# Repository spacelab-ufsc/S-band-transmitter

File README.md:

<h1 align="center">
	TRANSMITTER FOR S-BAND
	<br>
</h1>

<h4 align="center">Transmitter module designed to operate on S-band</h4>

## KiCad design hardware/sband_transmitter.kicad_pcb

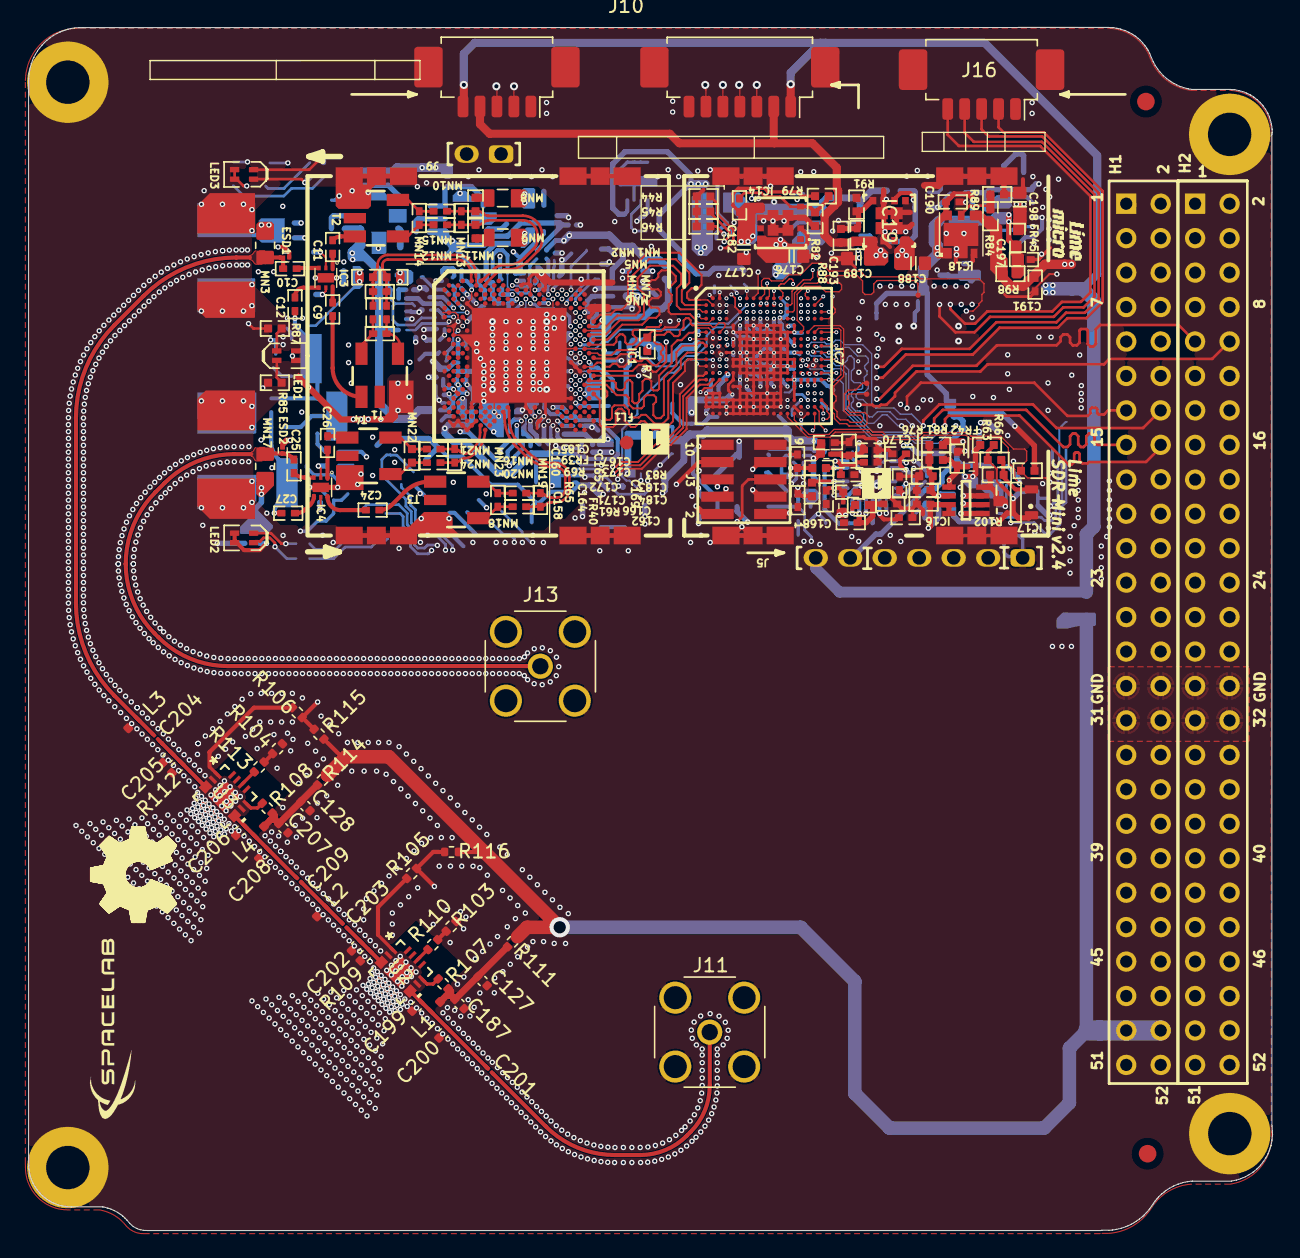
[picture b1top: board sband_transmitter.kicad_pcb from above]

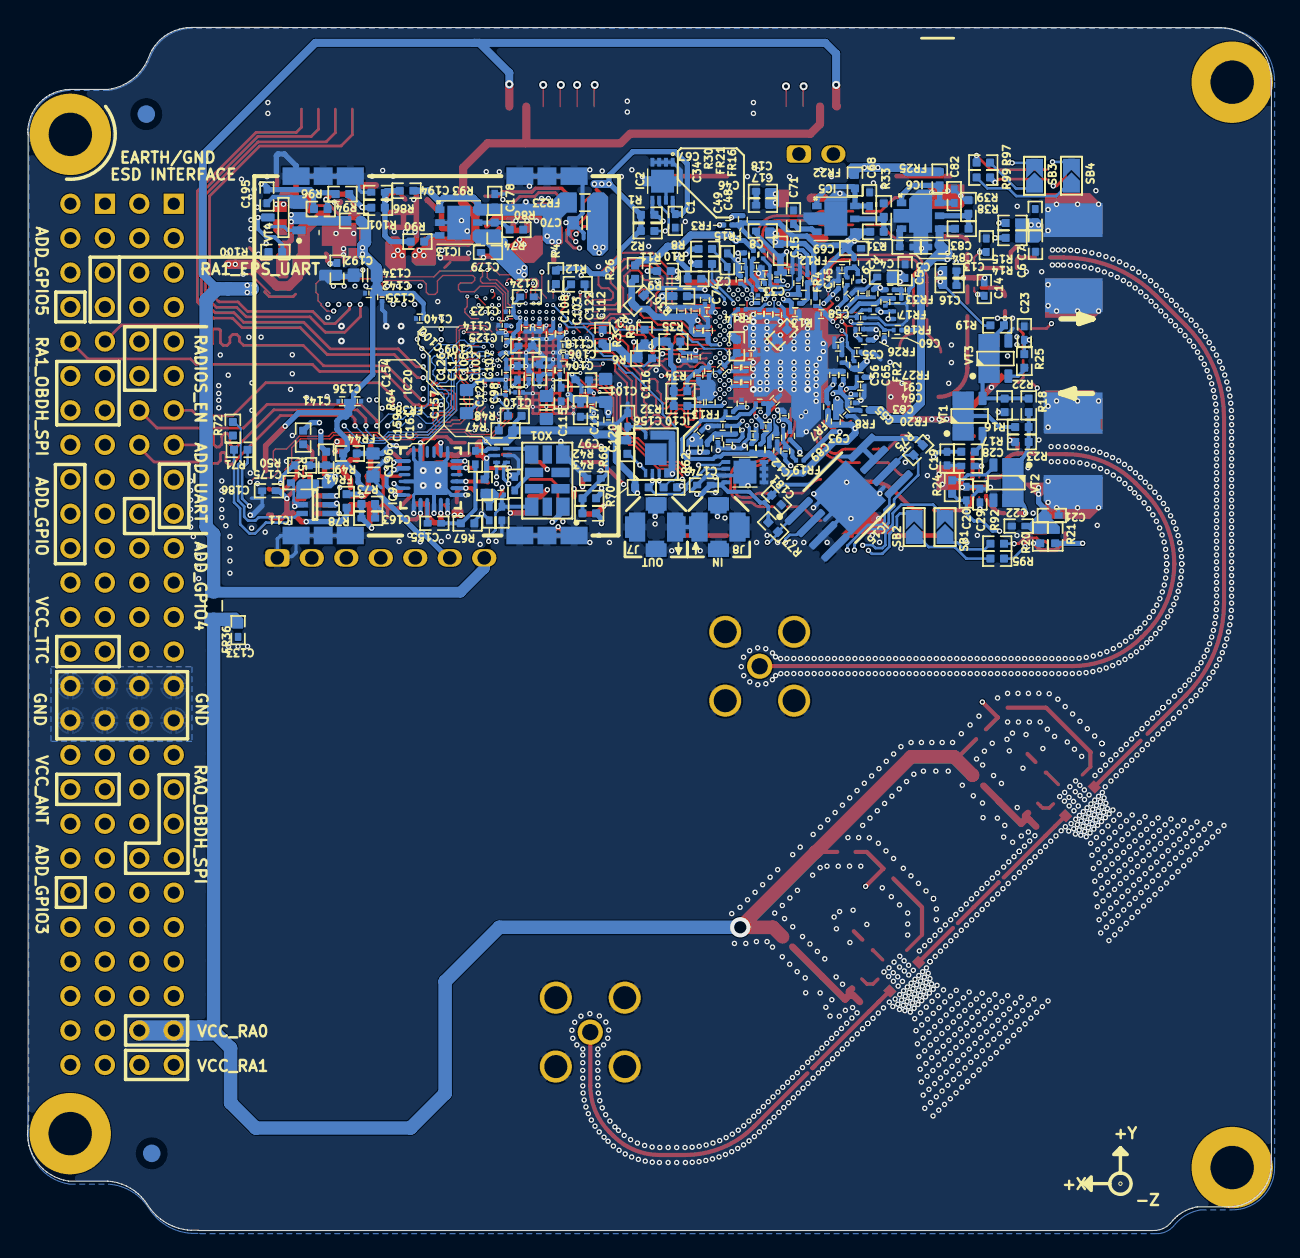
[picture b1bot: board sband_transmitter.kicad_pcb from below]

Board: 8 copper layers, 91.7 x 88.7 mm, 434 parts (278 on the bottom side), 218 nets.

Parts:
C1, C159, C164, C165, C194: 1uF, 25V; CAP0402
C2: 10pF, 25V; CAP0402
C3, C5, C7, C16, C17, C19, C20, C22, C23, C71, C84, C167, C168, C169, C170, C172, C173, C192: 100pF, 50V; CAP0402
C4, C6, C8, C15, C18, C21, C97, C133, C154, C155, C156, C161, C162, C163, C166, C171, C174, C175, C180, C181, C183, C185, C186, C195: 100nF, 16V; CAP0402
C9, C12, C24, C27, C158, C160: 47pF, 50V; CAP0402
C10, C11, C25, C26: 510pF; CAP0402
C13, C14, C28, C29, C102, C104, C109, C113, C115, C119, C124: 10nF, 50V; CAP0402
C30, C32, C33, C34, C35, C36, C37, C39, C41, C43, C44, C45, C46, C48, C49, C50, C51, C52, C53, C54, C55, C56, C57, C58, C59, C60, C62, C63, C64, C65, C66, C67, C73, C75, C77, C79, C81, C85, C86, C87, C88, C89, C90, C91, C92, C93, C94, C95, C96, C100, C111, C117, C122, C135, C141: 1uF, 6.3V; CAP0201
C31, C38, C40, C42, C47, C61, C72, C74, C76, C78, C80: 1nF, 10%; CAP0201
C68, C69, C82, C83, C178, C179, C190, C191, C197: 4.7uF, 6.3V; CAP0402
C70, C99, C116, C121, C134, C196, C198: 10uF, 6.3V; CAP0603
C98, C101, C103, C105, C106, C107, C108, C110, C112, C114, C118, C120, C123, C125, C126, C136, C140, C142: 100nF, 10V; CAP0201
C127, C128: 0.1uF; C_0402_1005Metric
C157: 18nF, 16V; CAP0402
C176, C177, C188, C189: 22uF, 10V; CAP0603
C182: 16pF, 50V; CAP0402
C184: 1nF, 50V; CAP0402
C187, C207: 100pF; C_0402_1005Metric
C193: 82pF, 50V; CAP0402
C199, C200, C206, C208: 1.5pF; C_0402_1005Metric
C201, C209: 27pF; C_01005_0402Metric
C202, C205: 2pF; C_0402_1005Metric
C203, C204: 1pF; C_01005_0402Metric
ESD1, ESD2: ESD8472; ESD8472_X3DFN2
FL1: Fiducial; Fiducial_local
FR1, FR2, FR3, FR4, FR5, FR6, FR7, FR8, FR9, FR10, FR11, FR12, FR13, FR14, FR15, FR16, FR17, FR18, FR19, FR20, FR21, FR24, FR26, FR27, FR28, FR29, FR30, FR31, FR32, FR33, FR34, FR38, FR39, FR40, FR41, FR42: 600R, 0.27A; RES0201
FR22, FR25, FR44, FR45: 220R, 0.9A; RES0402
FR23, FR36: 600R, 2A; RES0805
IC1: LMS7002M; LMS7002M_v5
IC2, IC12: M24128; M24128-DFMC6TG
IC3, IC4: SKY13411-374LF
IC5, IC6, IC13, IC18: LD39100PUR
IC7: LFE5U-45F-MG285; LFE5U-25F-8MG285C_LATTICE_FPGA
IC9: LMK00105; LMK00105SQ
IC10: LM75; HWSON8_LM75
IC11: DAC6311IDCK; AD5601_SOT23-6
IC14: LMZ20501SILR; LMZ20501SILR_DC-DC_8-SMD
IC15: W25Q128JVSIQ; S25FL164K_WSON8_DFN6
IC16: AD5662; AD5662_SOT23-8
IC17: AS431; SOT23-3_V3
IC19: LMZ20501SILR; SIL0008F
IC20: 74LVC1G3157FZ4; 74LVC1G3157FZ4_SPDT_SW_DFN1410-6
J3: FPGA GPIO; SWD_10_pin
J5: FPGA JTAG (board edge); HEADER7X1_TH_V2
J7, J8: U.FL/MMCX; MMCX_UFL_conn_u
J9: FAN; Header2x1_TH_v2
J10: PC104-Mainboard
J11, J13: Conn_Coaxial; CONN MCX JACK RA 50 OHM SMD
J12: FPGA JTAG (board edge); Molex_PicoBlade_53261-0771_1x07-1MP_P1.25mm_Horizontal
J15, J16: FPGA EGPIO (board edge); Molex_PicoBlade_53261-0571_1x05-1MP_P1.25mm_Horizontal
L1, L4: 18nH; L_0402_1005Metric
L2, L3: 6.2nH; L_0402_1005Metric
LED1, LED2, LED3: LED_RG; LED-2x0603
MECH2, MECH3, MECH4, MECH5, MECH6, MECH7, MECH8, MECH9, MECH11, MECH12, MECH13, MECH14: RFI Shield clip; RFI_SHIELD_CLPS_MINI
MECH10: RFI Shield; WurthElectronic_RF_shield
MECH15: RFI Shield; WURTHELECTRONIC_RF_SHIELD
MN1, MN2, MN22: 8.2nH, 5%; RES0402
MN3, MN17: 100uH; RES0805_0603
MN4, MN7: 0.8pF; CAP0402
MN5, MN13, MN19: 1pF; CAP0402
MN6, MN18: 0.5pF; CAP0402
MN8, MN9: 100uH; RES0805
MN10, MN11: 0R; RES0402
MN12, MN15: 100nF, 16V; CAP0402
MN14, MN16, MN20: 2pF; CAP0402
MN21, MN24: 510pF; CAP0402
MN23: 1.2pF; CAP0402
R1, R2: 2k2, 1%; RES0402
R3, R4, R5, R6, R7, R12, R13, R39, R62, R71, R73, R74, R77, R83, R84, R86: 10k, 1%; RES0402
R8, R9, R10, R11, R22, R23, R67: 49.9R, 1%; RES0402
R14, R15, R20, R21, R26, R27, R32, R34, R35, R36, R37, R42, R43, R44, R45, R46, R61, R65, R66, R69, R78, R90, R94, R96, R98, R100, R101, R102: 0R; RES0402
R16: 560R, 1%; RES0402
R17, R24, R25, R85, R87, R92, R95, R97, R99: 100R, 1%; RES0402
R18: 2.49k, 1%; RES0402
R19, R63, R68, R70, R75, R81: 1k, 1%; RES0402
R28, R29, R40, R41: 10R; RES0201
R30: 0R; RES0201
R31: 8.2k, 1%; RES0402
R33: 15k, 1%; RES0402
R38: 7.5k, 1%; RES0402
R47, R48, R49, R50, R51, R52, R89, R93: 4K7, 1%; RES0402
R64: 22R; RES0402
R72, R76: 3k, 1%; RES0402
R79: 80.6k, 1%; RES0402
R80: 27k, 1%; RES0402
R82: 40.2k, 1%; RES0402
R88: 237k, 1%; RES0402
R91: 52.3k, 1%; RES0402
R103, R104: 100k; R_0402_1005Metric
R105, R106: 22k; R_0402_1005Metric
R107, R108: 50R; R_0402_1005Metric
R109, R112: 15K; R_0402_1005Metric
R110, R111, R113, R114, R115, R116: 0R; R_0402_1005Metric
SB1, SB2, SB3, SB4: Solder bridge; SOLDER_BRIDGE_TRIANGULAR_V2
T1, T2, T3, T4: TC1-1-13M-45+; TC1-1-13MA+_JA4220-AL_
U2, U3: GRF5115; QFN-16_GRF
VT1, VT2, VT3: ZVN4525E6TA; ZVN4525E6_NMOS_SOT23-6
VT4: IRLML6244TRPBF; SOT23-3
XO1: E7355LF, 40MHz, w VC; RAKON_RTX5032A

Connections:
+1.8V_DIG_LMK: C164.2, C171.2, C172.2, C173.2, FR40.2, IC9.2 (Vddo), IC9.6 (Vddo)
+3.3V_DIG_LMK: C165.2, C166.2, C167.2, C168.2, C169.2, C170.2, FR39.2, IC9.8 (Vdd), IC9.14 (Vddo), IC9.18 (Vddo), IC9.23 (Vdd), R61.2
/05_LMS7002M_Misc/LMS_CORE_LDO_EN: IC1.U33 (CORE_LDO_EN), R7.1
/05_LMS7002M_Misc/LMS_I2C_SCL: IC1.C27 (SCL), IC2.6 (SCL), R2.2
/05_LMS7002M_Misc/LMS_I2C_SDA: IC1.D26 (SDA), IC2.5 (SDA), R1.2
/05_LMS7002M_Misc/LMS_RESET: IC1.E27 (RESET), R4.1
/05_LMS7002M_Misc/LMS_RXEN: IC1.V34 (RXEN), R6.2
/05_LMS7002M_Misc/LMS_TXEN: IC1.U29 (TXEN), R5.2
/05_LMS7002M_Misc/LMS_TXNRX1: IC1.V32 (TXNRX1), R3.1
/05_LMS7002M_Misc/LMS_TXNRX2: IC1.U31 (TXNRX2), R12.1
/06_LMS7002M_RF/RFSW_RX_V1: C29.2, IC4.5 (V1)
/06_LMS7002M_RF/RFSW_RX_V2: C28.2, IC4.2 (V2)
/06_LMS7002M_RF/RFSW_TX_V1: C14.2, IC3.5 (V1)
/06_LMS7002M_RF/RFSW_TX_V2: C13.2, IC3.2 (V2)
/06_LMS7002M_RF/RX: C25.2, ESD2.1, J13.1 (In), MN17.1
/06_LMS7002M_RF/RX1_H: C24.2, T3.3
/06_LMS7002M_RF/RX1_H_A_N: IC1.AJ15 (rfgn_h_RFE_1), MN19.1, MN20.2
/06_LMS7002M_RF/RX1_H_A_P: IC1.AK14 (rfgp_h_RFE_1), MN16.2, MN19.2
/06_LMS7002M_RF/RX1_H_B_N: MN18.1, MN20.1, T3.6
/06_LMS7002M_RF/RX1_H_B_P: MN16.1, MN18.2, T3.4
/06_LMS7002M_RF/RX1_W: C26.2, T4.3
/06_LMS7002M_RF/RX1_W_A_N: IC1.AP10 (rfgn_w_RFE_1), MN23.1, MN24.2
/06_LMS7002M_RF/RX1_W_A_P: IC1.AN9 (rfgp_w_RFE_1), MN21.2, MN23.2
/06_LMS7002M_RF/RX2_W_B_N: MN22.1, MN24.1, T4.6
/06_LMS7002M_RF/RX2_W_B_P: MN21.1, MN22.2, T4.4
/06_LMS7002M_RF/TX1_1: C9.2, T1.3
/06_LMS7002M_RF/TX1_1_A_N: IC1.A7 (pa1on_1), MN1.1, MN5.1, MN7.2
/06_LMS7002M_RF/TX1_1_A_P: IC1.B8 (pa1op_1), MN2.1, MN4.1, MN5.2
/06_LMS7002M_RF/TX1_1_B_N: MN6.2 (2_2), MN7.1, T1.6
/06_LMS7002M_RF/TX1_2: C11.2, T2.1
/06_LMS7002M_RF/TX2_1_A_N: IC1.B10 (pa2on_1), MN10.1, MN13.2, MN15.1
/06_LMS7002M_RF/TX2_1_A_P: IC1.A9 (pa2op_1), MN11.1, MN12.2, MN13.1
/06_LMS7002M_RF/TX2_1_B_N: MN14.1, MN15.2, T2.4
/06_LMS7002M_RF/TX2_1_B_P: MN12.1, MN14.2, T2.6
/06_LMS7002M_RF/TX_LB_AT: C19.1, R17.2
/06_LMS7002M_RF/TX_LB_SH: C20.1, C23.1, R24.1, R25.2
/08_FPGA/BOM_VER0: IC7.N1 (PR47D/LRC_GPLL0C_IN), R44.2
/08_FPGA/BOM_VER1: IC7.M1 (PR47C/LRC_GPLL0T_IN), R45.2
/08_FPGA/BOM_VER2: IC7.N2 (PR44D), R46.2
/08_FPGA/FPGA_EGPIO1: IC7.A8 (PT35B/PCLKC1_0), J15.3
/08_FPGA/FPGA_GPIO2: IC7.N16 (PB4B/D6/IO6), J3.3
/08_FPGA/FPGA_GPIO3: IC7.N17 (PB6A/D5/IO5), J3.4
/08_FPGA/FPGA_GPIO4: IC7.M18 (PB6B/D4/IO4), J3.5
/08_FPGA/FPGA_GPIO5: IC7.R18 (PB9B/D2/IO2), J3.6
/08_FPGA/FPGA_GPIO6: IC7.T17 (PB13B/CS1N), J3.7
/08_FPGA/FPGA_GPIO7: IC7.R17 (PB13A/SN/CSN), J3.8
/08_FPGA/FPGA_JTAG_TCK: IC7.U13 (TCK), J5.2, J12.6, R52.1 (1_1)
/08_FPGA/FPGA_JTAG_TDI: IC7.T13 (TDI), J5.5, J12.5, R49.2
/08_FPGA/FPGA_JTAG_TDO: IC7.V14 (TDO), J5.3, J12.3, R51.2
/08_FPGA/FPGA_JTAG_TMS: IC7.V13 (TMS), J5.4, J12.4, R50.2
/10_Misc/EN_VCC3P3: C194.2, IC19.2 (EN), R86.1, R90.2, R93.1
/10_Misc/FPGA_CFG_SPI_SCLK: IC15.6 (C), R75.1
/10_Misc/FPGA_CFG_SPI_SS: IC15.1 (S), R77.1
/10_Misc/FPGA_I2C_SCL: IC10.2 (SCL), IC12.6 (SCL), R70.2
/10_Misc/FPGA_I2C_SDA: IC10.1 (SDA), IC12.5 (SDA), R68.2
/10_Misc/FPGA_LED2_G: R92.2, SB1.1
/10_Misc/FPGA_LED2_R: R95.2, SB2.1
/10_Misc/FPGA_LED3_G: R97.2, SB3.1
/10_Misc/FPGA_LED3_R: R99.2, SB4.1
/10_Misc/FPGA_SPI_DAC_SS: IC11.1 (~SYNC), IC16.5 (~SYNC)
/10_Misc/FPGA_SPI_MOSI: IC11.3 (SDIN), IC16.7 (DIN)
/10_Misc/FPGA_SPI_SCLK: IC11.2 (SCLK), IC16.6 (SCLK)
/10_Misc/LM75_OS: IC10.3 (OS), R62.1
/10_Misc/PG_VCC1P1: IC13.3 (PG), R90.1
/10_Misc/REF_CLK_IN: IC20.1 (B1), J8.1 (X)
/10_Misc/REF_CLK_OUT: IC9.17 (CLKout4), J7.1 (X)
/10_Misc/RxPLL_CLK: C160.2, R69.1
/10_Misc/TCXO_DAC_VREF: C183.1, IC16.2 (Vref), R76.1, R78.2, R81.1, R83.1
/10_Misc/TxPLL_CLK: C158.2, R65.1
/10_Misc/XO_VC: C163.2, C184.1, IC16.3 (Vfb), IC16.4 (Vout), R71.1, R72.1, R73.1, XO1.1 (VCO)
/12_RF_Driver_PA/Driver-TX-Out: C203.1, C209.2, L2.1
Driver-Enable: IC7.N18 (PB9A/D3/IO3), J3.2, R106.1, R115.2
GND: C1.2, C2.2, C3.2, C4.1, C5.2, C6.1, C8.1, C13.1, C14.1, C15.1, C16.2, C17.2, C18.1, C19.2, C20.2, C21.1, C22.2, C23.2, C28.1, C29.1, C30.2, C31.2, C32.2, C33.2, C34.2, C35.1, C36.2, C37.2, C38.2, C39.2, C40.2, C41.2, C42.2, C43.2, C44.2, C45.2, C46.2, C47.2, C48.2, C49.1, C50.2, C51.2, C52.2, C53.2, C54.2, C55.2, C56.1, C57.2, C58.1, C59.1, C60.2, C61.2, C62.2, C63.2, C64.2, C65.2, C66.2, C67.2, C68.1, C69.1, C70.1, C71.1, C72.2, C73.2, C74.2, C75.2, C76.2, C77.2, C78.2, C79.2, C80.2, C81.2, C82.1, C83.1, C84.1, C85.2, C86.2, C87.2, C88.2, C89.2, C90.2, C91.2, C92.2, C93.2, C94.2, C95.2, C96.2, C97.1, C98.2, C99.1, C100.1, C101.2, C102.1, C103.2, C104.1, C105.2, C106.2, C107.2, C108.2, C109.1, C110.2, C111.1, C112.2, C113.1, C114.2, C115.1, C116.1, C117.1, C118.2, C119.1, C120.2, C121.1, C122.2, C123.2, C124.1, C125.2, C126.2, C127.2, C128.2, C134.1, C135.1, C136.2, C140.2, C141.1, C142.2, C156.2, C157.1, C158.1, C159.1, C160.1, C161.1, C162.1, C163.1, C164.1, C165.1, C166.1, C167.1, C168.1, C169.1, C170.1, C171.1, C172.1, C173.1, C174.2, C175.2, C176.1, C177.1, C178.1, C179.1, C180.2, C181.2, C183.2, C184.2, C185.1, C186.1, C187.2, C188.1, C189.1, C190.1, C191.1, C192.1, C194.1, C195.2, C196.1, C197.1, C198.1, C199.2, C200.2, C202.2, C205.2, C206.2, C207.2, C208.2, ESD1.2, ESD2.2, IC1.AA31 (DIGPRGND1), IC1.AF32 (DIGPRGND2), IC1.AG29 (DIGPRGND1), IC1.AJ7 (rfsn_l_RFE_2), IC1.AJ9 (rfsp_l_RFE_2), IC1.AJ19 (GND_CP_SXR), IC1.AK12 (rfsn_l_RFE_1), IC1.AK20 (GND_DIV_SXR), IC1.AL13 (rfsp_l_RFE_1), IC1.AL23 (GND_VCO_SXR), IC1.AM4 (rfgn_w_RFE_2), IC1.AM8 (rfgn_h_RFE_2), IC1.AM22 (DGND_SXR), IC1.AN3 (rfgp_w_RFE_2), IC1.AN5 (rfgp_l_RFE_2), IC1.AN7 (rfgp_h_RFE_2), IC1.AN25 (GND_RXBUF), IC1.AP6 (rfgn_l_RFE_2), IC1.B18 (DGND_CGEN), IC1.B20 (GND_CP_CGEN), IC1.C7 (GND_TLOBUF_TRF), IC1.C23 (GND_DIG), IC1.D20 (GND_DIV_CGEN), IC1.E25 (GND_SPI_BUF), IC1.F6 (GND_TXBUF), IC1.G31 (DIGPRGND2), IC1.GND (EP), IC1.H2 (GND_VCO_SXT), IC1.J33 (DIGPRGND1), IC1.K4 (GND_CP_SXT), IC1.L3 (GND_DIV_SXT), IC1.N3 (DGND_SXT), IC1.T30 (DIGPRGND1,2), IC1.V30 (LOGIC_RESET), IC1.W29 (DIGPRGND1), IC1.Y30 (DIGPRGND2), IC2.1 (E0), IC2.2 (E1), IC2.3 (E2), IC2.4 (VSS), IC2.7 (~WC), IC2.PAD, IC3.PAD, IC4.PAD, IC5.2 (GND), IC5.PAD, IC6.2 (GND), IC6.PAD, IC7.B3 (GND), IC7.E5 (GND), IC7.E7 (GND), IC7.E8 (GND), IC7.E9 (GND), IC7.E10 (GND), IC7.E11 (GND), IC7.E12 (GND), IC7.F5 (GND), IC7.F6 (GND), IC7.F7 (GND), IC7.F8 (GND), IC7.F9 (GND), IC7.F10 (GND), IC7.F11 (GND), IC7.F12 (GND), IC7.G2 (GND), IC7.G6 (GND), IC7.G7 (GND), IC7.G8 (GND), IC7.G9 (GND), IC7.G10 (GND), IC7.G11 (GND), IC7.G12 (GND), IC7.H6 (GND), IC7.H7 (GND), IC7.H8 (GND), IC7.H9 (GND), IC7.H10 (GND), IC7.H11 (GND), IC7.H12 (GND), IC7.J3 (PR29C/GR_PCLK3_1), IC7.J6 (GND), IC7.J7 (GND), IC7.J8 (GND), IC7.J9 (GND), IC7.J10 (GND), IC7.J11 (GND), IC7.J12 (GND), IC7.K5 (GND), IC7.K6 (GND), IC7.K7 (GND), IC7.K8 (GND), IC7.K9 (GND), IC7.K10 (GND), IC7.K11 (GND), IC7.L2 (GND), IC7.L5 (GND), IC7.L6 (GND), IC7.L7 (GND), IC7.L8 (GND), IC7.L9 (GND), IC7.L10 (GND), IC7.L11 (GND), IC7.L17 (GND), IC7.M6 (GND), IC7.M7 (GND), IC7.M8 (GND), IC7.M9 (GND), IC7.M10 (GND), IC7.M11 (GND), IC7.N7 (GND), IC7.N8 (GND), IC7.N9 (GND), IC7.N10 (GND), IC7.N11 (GND), IC7.P5 (GND), IC7.P6 (GND), IC7.P8 (GND), IC7.P10 (GND), IC7.P12 (GND), IC7.R1 (GND), IC7.R2 (GND), IC7.R3 (GND), IC7.R10 (GND), IC7.T1 (GND), IC7.T2 (GND), IC7.T3 (GND), IC7.T4 (GND), IC7.T5 (GND), IC7.T6 (GND), IC7.T7 (GND), IC7.T8 (GND), IC7.T9 (GND), IC7.T10 (GND), IC7.T11 (GND), IC7.T12 (GND), IC7.U1 (GND), IC7.U2 (GND), IC7.U3 (GND), IC7.U4 (GND), IC7.U5 (GND), IC7.U6 (GND), IC7.U7 (GND), IC7.U8 (GND), IC7.U9 (GND), IC7.U10 (GND), IC7.U11 (GND), IC7.U12 (GND), IC7.U14 (CFG_0), IC7.V4 (GND), IC7.V5 (GND), IC7.V6 (GND), IC7.V7 (GND), IC7.V8 (GND), IC7.V9 (GND), IC7.V10 (GND), IC7.V15 (CFG_2), IC9.1 (GND), IC9.7 (GND), IC9.11 (GND), IC9.12 (GND), IC9.16 (GND), IC9.19 (GND), IC9.22 (SEL), IC9.25 (GND), IC10.4 (GND), IC10.5 (A2), IC10.6 (A1), IC10.7 (A0), IC11.5 (GND), IC12.1 (E0), IC12.2 (E1), IC12.3 (E2), IC12.4 (VSS), IC12.7 (~WC), IC12.PAD, IC13.2 (GND), IC13.PAD, IC14.3 (MODE), IC14.6 (GND), IC14.PAD (EP_(GND)), IC15.3 (W), IC15.4 (GND), IC15.PAD (GND), IC16.8 (GND), IC17.3 (NC/A), IC18.2 (GND), IC18.PAD, IC19.3 (MODE), IC19.6 (GND), IC20.2 (GND), J3.9, J5.1, J7.2 (Y), J8.2 (Y), J10.H1-29 (Pin_29), J10.H1-30 (Pin_30), J10.H1-31 (Pin_31), J10.H1-32 (Pin_32), J10.H2-29 (Pin_29), J10.H2-30 (Pin_30), J10.H2-31 (Pin_31), J10.H2-32 (Pin_32), J11.2 (Ext), J12.7, J13.2 (Ext), J15.1, J16.1, L2.2, L3.2, MECH2.1 (GND_1), MECH3.1 (GND_1), MECH4.1 (GND_1), MECH5.1 (GND_1), MECH6.1 (GND_1), MECH7.1 (GND_1), MECH8.1 (GND_1), MECH9.1 (GND_1), MECH11.1 (GND_1), MECH12.1 (GND_1), MECH13.1 (GND_1), MECH14.1 (GND_1), R12.2, R13.2, R22.1, R23.1, R33.1, R39.1, R44.1, R45.1, R46.1, R67.1, R73.2, R80.2, R82.1, R83.2, R89.2, R91.1, R100.1, R102.2, R103.1, R104.1, R109.2, R112.2, T1.1, T2.3, T3.1, T4.1, U2.2 (GND/NC), U2.5 (GND/NC), U2.6 (GND/NC), U2.7 (GND/NC), U2.8 (GND/NC), U2.11 (GND/NC), U2.17 (GND), U3.2 (GND/NC), U3.5 (GND/NC), U3.6 (GND/NC), U3.7 (GND/NC), U3.8 (GND/NC), U3.11 (GND/NC), U3.17 (GND), VT2.4 (S), VT3.4 (S), VT4.S, XO1.4 (GND)
GPIO-1: IC7.A16 (PL20B), J16.5
GPIO-2: IC7.D18 (PL26C/PCLKT6_0), J16.4
GPIO-3: IC7.G16 (PL29D), J16.3
GPIO-4: IC7.G18 (PL32A), J16.2
I2C_SCL_DATA: IC7.K15 (PL41D), J10.H2-9 (Pin_9)
I2C_SDA_DATA: IC7.K17 (PL44A), J10.H2-10 (Pin_10)
unnamed: C6.2, C7.1 (1_1), MN3.2, R14.2, R15.2
unnamed: C21.2, C22.1, MN17.2, R20.2, R21.2
unnamed: C27.2, R16.1, R18.2, R23.2, VT2.1 (D), VT2.2 (D), VT2.5 (D), VT2.6 (D)
unnamed: C30.1, C31.1, C37.1, C38.1, C39.1, C40.1, C41.1, C42.1, IC1.AA29 (DIGPRVDD1), IC1.AE29 (DIGPRVDD1), IC1.L33 (DIGPRVDD1), IC1.R31 (DIGPRVDD1), R26.2, R27.2
unnamed: C59.2, FR12.1, R28.2, R29.2
unnamed: C74.1, C75.1, IC1.H32 (DIGPRVDD2), R36.2
unnamed: C76.1, C77.1, IC1.T32 (DIGPRVDD2), R35.2
unnamed: C78.1, C79.1, IC1.W33 (DIGPRVDD2), R34.2
unnamed: C80.1, C81.1, IC1.AH30 (DIGPRVDD2), R32.2
unnamed: C95.1, FR34.2, R41.2
unnamed: C96.1, FR33.1, R40.1
unnamed: C97.2, J3.10, R42.2, R43.2
unnamed: C127.1, C187.1, L1.1, R107.2, R111.2
unnamed: C128.1, C207.1, L4.1, R108.2, R114.2
unnamed: C154.1, C155.2, R67.2
unnamed: C159.2, FR38.1, R64.1
unnamed: C195.1, J9.2, R94.2, R96.2
unnamed: C199.1, C200.1, C201.1, L1.2, U2.9 (RF_OUT/VDD), U2.10 (RF_OUT/VDD)
unnamed: C202.1, C203.2, R109.1, U2.3 (RF_IN), U2.4 (RF_IN)
unnamed: C204.2, C205.1, R112.1, U3.3 (RF_IN), U3.4 (RF_IN)
unnamed: C206.1, C208.1, C209.1, L4.2, U3.9 (RF_OUT/VDD), U3.10 (RF_OUT/VDD)
unnamed: C2.1, IC1.C29 (SCLK), R8.1
unnamed: IC1.F30 (SDIO), R9.1
unnamed: IC1.F28 (SDO), R10.1
unnamed: IC1.D28 (SEN), R11.1
unnamed: IC1.F18 (vr_rext), R13.1
unnamed: C72.1, C73.1, IC1.W31 (DIGPRPOC), R37.2
unnamed: C88.1, FR30.1, IC1.E17 (VDD18_BIAS)
unnamed: C67.1, IC1.D24 (VDD18_DIG), R30.1
unnamed: C91.1, FR27.2, IC1.AE3 (VDD18_TIA_RFE), IC1.AF4 (VDD18_LDO_RX)
unnamed: C92.1, FR26.2, IC1.N1 (VDD18_LDO_TX)
unnamed: C93.1, FR34.1, IC1.AM26 (VDD18_RXBUF)
unnamed: C90.1, FR28.1, IC1.AM18 (VDD18_SXR)
unnamed: C87.1, FR31.1, IC1.D16 (VDD18_TRF)
unnamed: C94.1, FR33.2, IC1.H6 (VDD18_TXBUF)
unnamed: C86.1, FR32.1, IC1.E21 (VDD18_VCO_CGEN)
unnamed: C89.1, FR29.1, IC1.AK22 (VDD18_VCO_SXR)
unnamed: C85.1, FR24.1, IC1.G3 (VDD18_VCO_SXT)
unnamed: C32.1, C33.1, C34.1, FR3.1, IC1.A17 (DVDD_CGEN), IC1.C25 (VDD12_DIG), IC1.F24 (VDD_SPI_BUF)
unnamed: C36.1, FR1.1, IC1.AL21 (DVDD_SXR)
unnamed: C35.2, FR2.1, IC1.M4 (DVDD_SXT)
unnamed: C58.2, FR4.1, IC1.J5 (VDD12O_VCO_SXT), IC1.K6 (VDD12_VCO_SXT)
unnamed: C55.1, FR8.1, IC1.AG5 (VDD12_LNA_RFE)
unnamed: C51.1, IC1.AP26 (VDD12_RXBUF), R29.1
unnamed: C56.2, FR7.1, IC1.AD6 (VDD12_TIA_RFE)
unnamed: C43.1, IC1.G5 (VDD12_TXBUF), R28.1
unnamed: C52.1, FR11.1, IC1.AN23 (VDD12_VCO_SXR)
unnamed: C63.1, C64.1, C65.1, FR20.1, IC1.AD4 (VDD14_RBB), IC1.AF2 (VDD14_TIA_RFE), IC1.AF6 (VDD14_LNA_RFE)
unnamed: C61.1, C62.1, FR21.1, IC1.C21 (VDD14_VCO_CGEN)
unnamed: C60.1, FR18.1, IC1.K2 (VDDO_DIV_SXT), IC1.L5 (VDD_DIV_SXT)
unnamed: C45.1, FR17.1, IC1.D6 (VDDO_TLOBUF_TRF), IC1.F8 (VDD_TLOBUF_TRF)
unnamed: C50.1, FR13.1, IC1.AJ25 (VDD_AFE)
unnamed: C49.2, FR14.1, IC1.F20 (VDD_CP_CGEN)
unnamed: C54.1, FR9.1, IC1.AL19 (VDD_CP_SXR)
unnamed: C57.1, FR5.1, IC1.J3 (VDD_CP_SXT)
unnamed: C47.1, C48.1, FR15.1, IC1.E19 (VDD_DIV_CGEN)
unnamed: C53.1, FR10.1, IC1.AM20 (VDD_DIV_SXR)
unnamed: C66.1, FR19.1, IC1.AN17 (VDD_MXLOBUF_RFE)
unnamed: C44.1, FR6.1, IC1.P4 (VDD_TBB)
unnamed: C46.1, FR16.1, IC1.B16 (VDD_TPAD_TRF)
unnamed: C9.1, IC3.6 (ANT1)
unnamed: C11.1, IC3.1 (ANT2)
unnamed: C10.1, IC3.3 (RX)
unnamed: C12.1, IC3.4 (TX)
unnamed: C24.1, IC4.6 (ANT1)
unnamed: C26.1, IC4.1 (ANT2)
unnamed: C25.1, IC4.3 (RX)
unnamed: C27.1, IC4.4 (TX)
unnamed: IC5.5 (ADJ), R31.1, R33.2
unnamed: C68.2, FR22.2, IC5.1 (EN), IC5.6 (Vin)
unnamed: C71.2, IC5.3 (PG)
unnamed: IC6.5 (ADJ), R38.1, R39.2
unnamed: C82.2, FR25.2, IC6.1 (EN), IC6.6 (Vin)
unnamed: C84.2, IC6.3 (PG)
unnamed: IC7.V16 (INITN), R47.2
unnamed: IC7.T15 (PROGRAMN), R48.2
unnamed: C155.1, IC9.21 (CLKin)
unnamed: C162.2, IC9.20 (CLKin*)
unnamed: IC9.3 (CLKout0), R65.2
unnamed: IC9.5 (CLKout1), R69.2
unnamed: IC9.24 (OE), R61.1
unnamed: C175.1, FR41.2, IC11.4 (VDD)
unnamed: IC11.6 (VOUT), R72.2
unnamed: IC13.5 (ADJ), R74.1, R80.1
unnamed: C182.2, IC14.4 (FB), R79.1, R82.2
unnamed: C180.1, FR42.2, IC16.1 (Vdd), R76.2
unnamed: IC17.2 (A), R66.2, R102.1
unnamed: IC18.5 (ADJ), R84.1, R89.1
unnamed: C192.2, IC18.3 (PG)
unnamed: C193.2, IC19.4 (FB), R88.1, R91.2
unnamed: C154.2, IC20.4 (A)
unnamed: IC20.3 (B0), XO1.6 (RF_OUT)
unnamed: J9.1, R100.2, VT4.D
unnamed: C201.2, J11.1 (In)
unnamed: LED1.3, R85.1
unnamed: LED1.4, R87.1
unnamed: LED2.3, R92.1
unnamed: LED2.4, R95.1
unnamed: LED3.3, R97.1
unnamed: LED3.4, R99.1
unnamed: MN8.1, MN10.2
unnamed: MN9.1, MN11.2
unnamed: R16.2, VT1.1 (D), VT1.2 (D), VT1.5 (D), VT1.6 (D)
unnamed: R103.2, R110.1
unnamed: R104.2, R113.1
unnamed: R110.2, U2.14 (BIAS1)
unnamed: R107.1, U2.12 (BIAS2)
unnamed: R105.2, U2.1 (VENABLE)
unnamed: R113.2, U3.14 (BIAS1)
unnamed: R108.1, U3.12 (BIAS2)
unnamed: R106.2, U3.1 (VENABLE)
unnamed: R17.1, VT1.3 (G)
unnamed: C12.2, R18.1, R19.1, R22.2, VT1.4 (S), VT3.1 (D), VT3.2 (D), VT3.5 (D), VT3.6 (D)
unnamed: R24.2, VT2.3 (G)
unnamed: R25.1, VT3.3 (G)
unnamed: C157.2, XO1.7 (VC_FILTER)
PA-Enable: IC7.N15 (PB4A/D7/IO7), J3.1, R105.1, R116.2
SPI_CS_N/SS_N_DATA: IC7.L16 (PL44D), J10.H1-16 (Pin_16)
SPI_MISO_DATA: IC7.J16 (PL35D), J10.H1-15 (Pin_15)
SPI_MOSI_DATA: IC7.H16 (PL35C), J10.H1-14 (Pin_14)
SPI_SCK_DATA: IC7.K16 (PL41C), J10.H1-13 (Pin_13)
TX: C10.2, C204.1, ESD1.1, L3.1, MN3.1
VCC1P1: C99.2, C100.2, C101.1, C102.2, C103.1, C104.2, C105.1, C106.1, C107.1, C108.1, C109.2, C179.2, IC7.D8 (VCC), IC7.D9 (VCC), IC7.D10 (VCC), IC7.D11 (VCC), IC7.J4 (VCC), IC7.J5 (VCC), IC7.J14 (VCC), IC7.J15 (VCC), IC7.M4 (VCC), IC7.M15 (VCC), IC7.P7 (VCC), IC7.P9 (VCC), IC7.P11 (VCC), IC13.4 (Vout), R74.2
VCC1P4_LMS: C83.2, FR18.2, FR19.2, FR20.2, FR21.2, IC6.4 (Vout), R26.1, R38.2
VCC1P8: C177.2, C178.2, C182.1, FR23.1, FR40.1, IC13.1 (EN), IC13.6 (Vin), IC14.5 (VOUT), R62.2, R79.2, R93.2
VCC1P8_LMS: C3.1, C4.2, C5.1, C8.2, C15.2, C16.1, C17.1, C18.2, C70.2, FR22.1, FR23.2, FR24.2, FR25.1, FR26.1, FR27.1, FR28.2, FR29.2, FR30.2, FR31.2, FR32.2, MN1.2, MN2.2, MN8.2, MN9.2, R19.2, R30.2, R40.2, R41.1
VCC1P25_LMS: C69.2, FR1.2, FR2.2, FR3.2, FR4.2, FR5.2, FR6.2, FR7.2, FR8.2, FR9.2, FR10.2, FR11.2, FR12.2, FR13.2, FR14.2, FR15.2, FR16.2, FR17.2, IC5.4 (Vout), R27.1, R31.2
VCC2P5: C111.2, C112.1, C113.2, C114.1, C115.2, C191.2, IC7.E6 (VCCAUX), IC7.E13 (VCCAUX), IC7.N6 (VCCAUX), IC7.P13 (VCCAUX), IC18.4 (Vout), R81.2, R84.2, R98.1
VCC2P5_VREF: C186.2, IC17.1 (K), R63.1, R66.1, R78.1
VCC3P3: C98.1, C110.1, C121.2, C122.1, C123.1, C124.2, C125.1, C126.1, C134.2, C135.2, C136.1, C140.1, C141.2, C142.1, C156.1, C174.1, C181.1, C189.2, C190.2, C193.1, FR44.1, IC7.D7 (VCCIO1), IC7.D12 (VCCIO0), IC7.G14 (VCCIO7), IC7.H14 (VCCIO7), IC7.M14 (VCCIO6), IC7.N13 (VCCIO8), IC7.N14 (VCCIO6), IC7.P14 (VCCIO8), IC7.T14 (CFG_1), IC10.8 (VCC), IC12.8 (VCC), IC15.7 (HOLD), IC15.8 (VCC), IC18.1 (EN), IC18.6 (Vin), IC19.5 (VOUT), J5.6, J12.2, J15.4, LED1.1, LED1.2, LED2.1, LED2.2, LED3.1, LED3.2, R14.1, R20.1, R42.1, R47.1, R48.1, R49.1, R50.1, R51.1, R68.1, R70.1, R75.2, R77.2, R88.2, R96.1, R101.1
VCC3P3_CLK: C185.2, C196.2, FR39.1, FR41.1, FR42.1, FR44.2, IC20.5 (VCC), R63.2, R64.2
VCC3P3_XO: C161.2, FR38.2, R71.2, XO1.9 (VCC)
VCC5P0: C176.2, C188.2, FR36.2, IC14.2 (EN), IC14.8 (VIN), IC19.8 (VIN), J5.7, J12.1, J15.5, R15.1, R21.1, R43.1, R86.2, R94.1
VCC_3V3: J10.H2-27 (Pin_27), J10.H2-28 (Pin_28)
VCC_3V3_ANT: J10.H2-35 (Pin_35), J10.H2-36 (Pin_36)
VCC_5V_RA_0: C133.1 (1_1), FR36.1, J10.H1-49 (Pin_49), J10.H1-50 (Pin_50), R111.1, R114.1, R115.1, R116.1
VCC_6V_RA_1: J10.H1-51 (Pin_51), J10.H1-52 (Pin_52)
VDIO_LMS: C1.1, C198.2, FR45.2, IC2.8 (VCC), R1.1, R2.1, R3.2, R4.2, R5.1, R6.1, R7.2, R32.1, R34.1, R35.1, R36.1, R37.1
VDIO_LMS_FPGA: C116.2, C117.2, C118.1, C119.2, C120.1, C197.2, FR45.1, IC7.G5 (VCCIO2), IC7.H5 (VCCIO2), IC7.M5 (VCCIO3), IC7.N5 (VCCIO3), R98.2, R101.2

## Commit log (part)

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2026-06-03 Adding README file
2026-06-03 Adding initial project
